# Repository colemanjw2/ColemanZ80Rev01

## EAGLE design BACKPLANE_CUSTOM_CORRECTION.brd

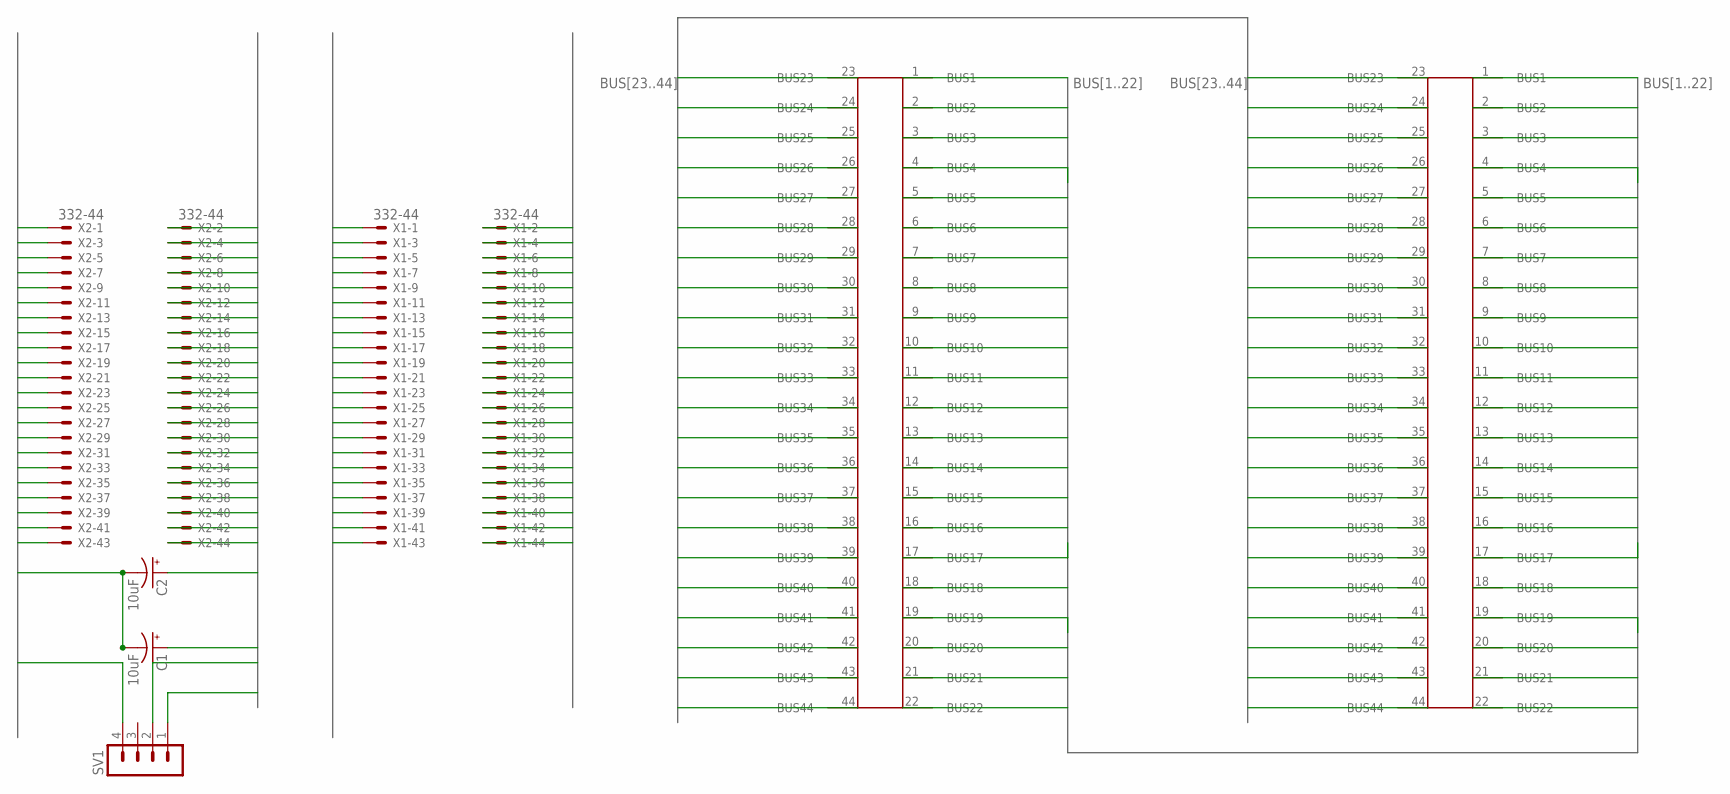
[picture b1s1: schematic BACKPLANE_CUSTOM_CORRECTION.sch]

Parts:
C1, C2: 10uF; CPOL-RADIAL-2.5MM-5MM
SV1: MA04-1
U$2, U$3: 22EDGECONNECTOR
X1, X2: 332-44

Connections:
BUS1: U$2.1 (BUS1), U$3.1 (BUS1), X1.2, X2.2
BUS2: U$2.2 (BUS2), U$3.2 (BUS2), X1.4, X2.4
BUS3: U$2.3 (BUS3), U$3.3 (BUS3), X1.6, X2.6
BUS4: U$2.4 (BUS4), U$3.4 (BUS4), X1.8, X2.8
BUS5: U$2.5 (BUS5), U$3.5 (BUS5), X1.10, X2.10
BUS6: U$2.6 (BUS6), U$3.6 (BUS6), X1.12, X2.12
BUS7: U$2.7 (BUS7), U$3.7 (BUS7), X1.14, X2.14
BUS8: U$2.8 (BUS8), U$3.8 (BUS8), X1.16, X2.16
BUS9: U$2.9 (BUS9), U$3.9 (BUS9), X1.18, X2.18
BUS10: U$2.10 (BUS10), U$3.10 (BUS10), X1.20, X2.20
BUS11: U$2.11 (BUS11), U$3.11 (BUS11), X1.22, X2.22
BUS12: U$2.12 (BUS12), U$3.12 (BUS12), X1.24, X2.24
BUS13: U$2.13 (BUS13), U$3.13 (BUS13), X1.26, X2.26
BUS14: U$2.14 (BUS14), U$3.14 (BUS14), X1.28, X2.28
BUS15: U$2.15 (BUS15), U$3.15 (BUS15), X1.30, X2.30
BUS16: U$2.16 (BUS16), U$3.16 (BUS16), X1.32, X2.32
BUS17: U$2.17 (BUS17), U$3.17 (BUS17), X1.34, X2.34
BUS18: U$2.18 (BUS18), U$3.18 (BUS18), X1.36, X2.36
BUS19: U$2.19 (BUS19), U$3.19 (BUS19), X1.38, X2.38
BUS20: U$2.20 (BUS20), U$3.20 (BUS20), X1.40, X2.40
BUS21: C1.1 (+), SV1.2, U$2.21 (BUS21), U$3.21 (BUS21), X1.42, X2.42
BUS22: C2.1 (+), SV1.1, U$2.22 (BUS22), U$3.22 (BUS22), X1.44, X2.44
BUS23: U$2.23 (BUS23), U$3.23 (BUS23), X1.1, X2.1
BUS24: U$2.24 (BUS24), U$3.24 (BUS24), X1.3, X2.3
BUS25: U$2.25 (BUS25), U$3.25 (BUS25), X1.5, X2.5
BUS26: U$2.26 (BUS26), U$3.26 (BUS26), X1.7, X2.7
BUS27: U$2.27 (BUS27), U$3.27 (BUS27), X1.9, X2.9
BUS28: U$2.28 (BUS28), U$3.28 (BUS28), X1.11, X2.11
BUS29: U$2.29 (BUS29), U$3.29 (BUS29), X1.13, X2.13
BUS30: U$2.30 (BUS30), U$3.30 (BUS30), X1.15, X2.15
BUS31: U$2.31 (BUS31), U$3.31 (BUS31), X1.17, X2.17
BUS32: U$2.32 (BUS32), U$3.32 (BUS32), X1.19, X2.19
BUS33: U$2.33 (BUS33), U$3.33 (BUS33), X1.21, X2.21
BUS34: U$2.34 (BUS34), U$3.34 (BUS34), X1.23, X2.23
BUS35: U$2.35 (BUS35), U$3.35 (BUS35), X1.25, X2.25
BUS36: U$2.36 (BUS36), U$3.36 (BUS36), X1.27, X2.27
BUS37: U$2.37 (BUS37), U$3.37 (BUS37), X1.29, X2.29
BUS38: U$2.38 (BUS38), U$3.38 (BUS38), X1.31, X2.31
BUS39: U$2.39 (BUS39), U$3.39 (BUS39), X1.33, X2.33
BUS40: U$2.40 (BUS40), U$3.40 (BUS40), X1.35, X2.35
BUS41: U$2.41 (BUS41), U$3.41 (BUS41), X1.37, X2.37
BUS42: U$2.42 (BUS42), U$3.42 (BUS42), X1.39, X2.39
BUS43: U$2.43 (BUS43), U$3.43 (BUS43), X1.41, X2.41
BUS44: C1.2 (-), C2.2 (-), SV1.4, U$2.44 (BUS44), U$3.44 (BUS44), X1.43, X2.43

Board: 2 copper layers, 7 parts (0 on the bottom side), 44 nets, no tracks yet.

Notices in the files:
parts and their libraries:
SparkFun-Capacitors: Licensing: Creative Commons ShareAlike 4.0 International - https://creativecommons.org/licenses/by-sa/4.0
